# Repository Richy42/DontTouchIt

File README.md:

# DontTouchIt
Is an inductive distance sensor board based on the TI LDC1614 chip.

It is intended for 3d Printers to measure the distance to the printing bed.
It speeds up quad gantry levelling and bed mesh calibration as no z movement is needed to get the distance between the probe and the bed.

As it supports three sensors it could probably be used also for homing.

## The board

### Coils cut away and one mounted on an angle

### 3d Printed case in the size similar to an Omron (like) probe

### Mounted on an Voron 2.4

## Klipper 3D support
I added experimental support to klipper and the following video shows a Quad Gantry Level run
https://youtu.be/B2gruTA73uU

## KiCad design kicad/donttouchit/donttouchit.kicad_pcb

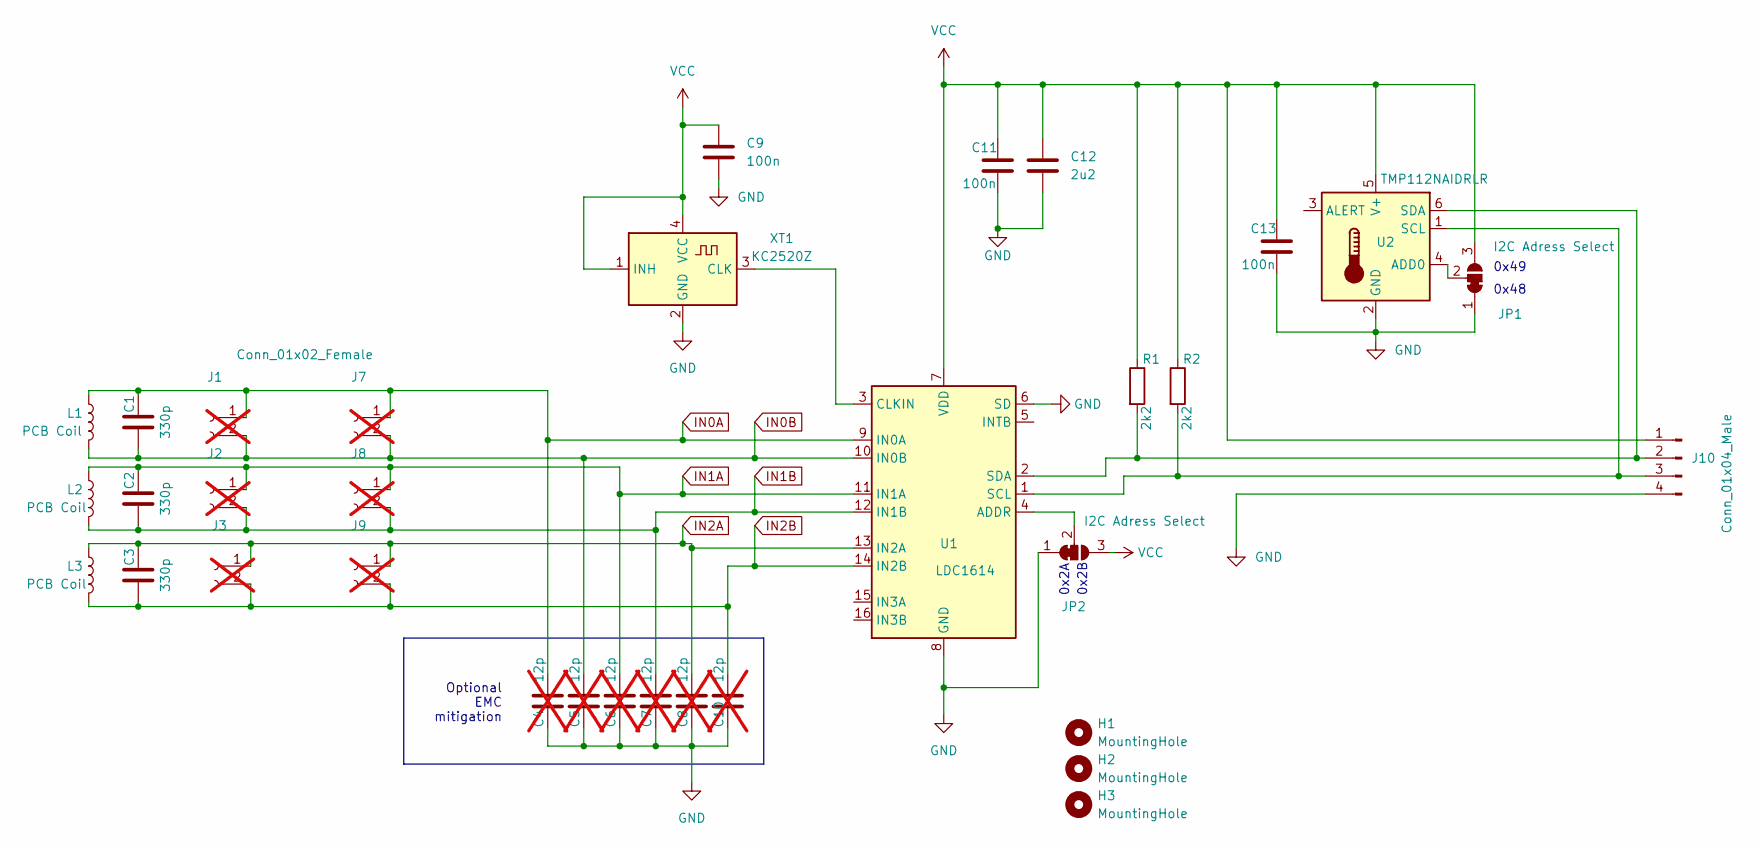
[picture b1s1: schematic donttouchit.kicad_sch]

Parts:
C1, C2, C3: 330p; C_0603_1608Metric_Pad1.08x0.95mm_HandSolder
C4, C5, C6, C7, C8, C10: 12p; C_0603_1608Metric_Pad1.08x0.95mm_HandSolder; not fitted
C9, C11, C13: 100n; C_0603_1608Metric_Pad1.08x0.95mm_HandSolder
C12: 2u2; C_0603_1608Metric_Pad1.08x0.95mm_HandSolder
H1, H2, H3: MountingHole; MountingHole_3.5mm
J1, J2, J3, J7, J8, J9: Conn_01x02_Female; PCBConnPadsTHT; not fitted
J10: Conn_01x04_Male; JST_PH_B4B-PH-SM4-TB_1x04-1MP_P2.00mm_Vertical
JP1, JP2: I2C Adress Select; SolderJumper-3_P1.3mm_Bridged12_RoundedPad1.0x1.5mm
L1, L2, L3: PCB Coil; Coil_14x14
R1, R2: 2k2; R_0603_1608Metric_Pad0.98x0.95mm_HandSolder
U1: LDC1614; WQFN-16-1EP_4x4mm_P0.5mm_EP2.6x2.6mm_ThermalVias
U2: TMP112NAIDRLR; SOT-563
XT1: KC2520Z; Oscillator_SMD_Kyocera_KC2520Z-4Pin_2.5x2.0mm

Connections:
GND: C4.2, C5.2, C6.2, C7.2, C8.2, C9.2, C10.2, C11.2, C12.2, C13.2, J10.4, JP1.1 (A), JP2.1 (A), U1.6 (SD), U1.8 (GND), U1.17 (GND), U2.2 (GND), XT1.2 (GND)
IN0A: C1.2, C4.1, J1.1, J7.1, L1.1, U1.9 (IN0A)
IN0B: C1.1, C5.1, J1.2, J7.2, L1.2, U1.10 (IN0B)
IN1A: C2.2, C6.1, J2.1, J8.1, L2.1, U1.11 (IN1A)
IN1B: C2.1, C7.1, J2.2, J8.2, L2.2, U1.12 (IN1B)
IN2A: C3.2, C8.1, J3.1, J9.1, L3.1, U1.13 (IN2A)
IN2B: C3.1, C10.1, J3.2, J9.2, L3.2, U1.14 (IN2B)
unnamed: J10.2, R1.2, U1.2 (SDA), U2.6 (SDA)
unnamed: J10.3, R2.2, U1.1 (SCL), U2.1 (SCL)
unnamed: JP1.2 (C), U2.4 (ADD0)
unnamed: JP2.2 (C), U1.4 (ADDR)
unnamed: U1.3 (CLKIN), XT1.3 (CLK)
VCC: C9.1, C11.1, C12.1, C13.1, J10.1, JP1.3 (B), JP2.3 (B), R1.1, R2.1, U1.7 (VDD), U2.5 (V+), XT1.1 (INH), XT1.4 (VCC)

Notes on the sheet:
0x48
0x2B
Optional EMC mitigation
0x2A
0x49

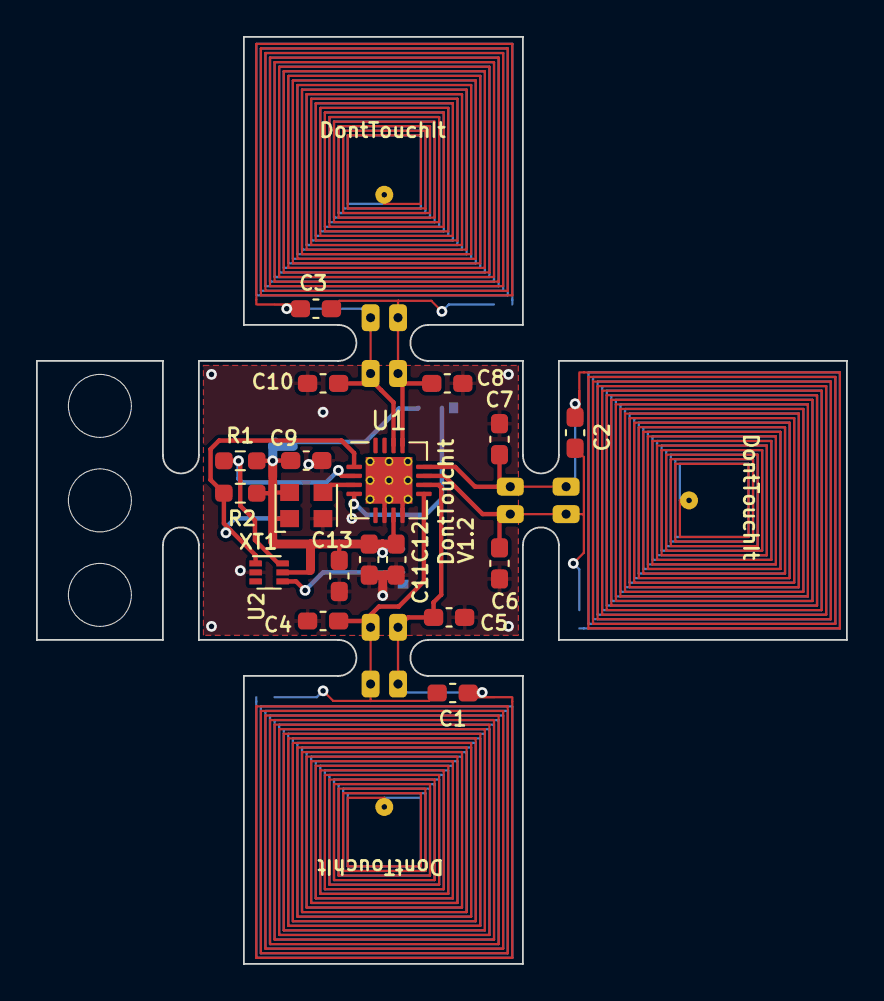
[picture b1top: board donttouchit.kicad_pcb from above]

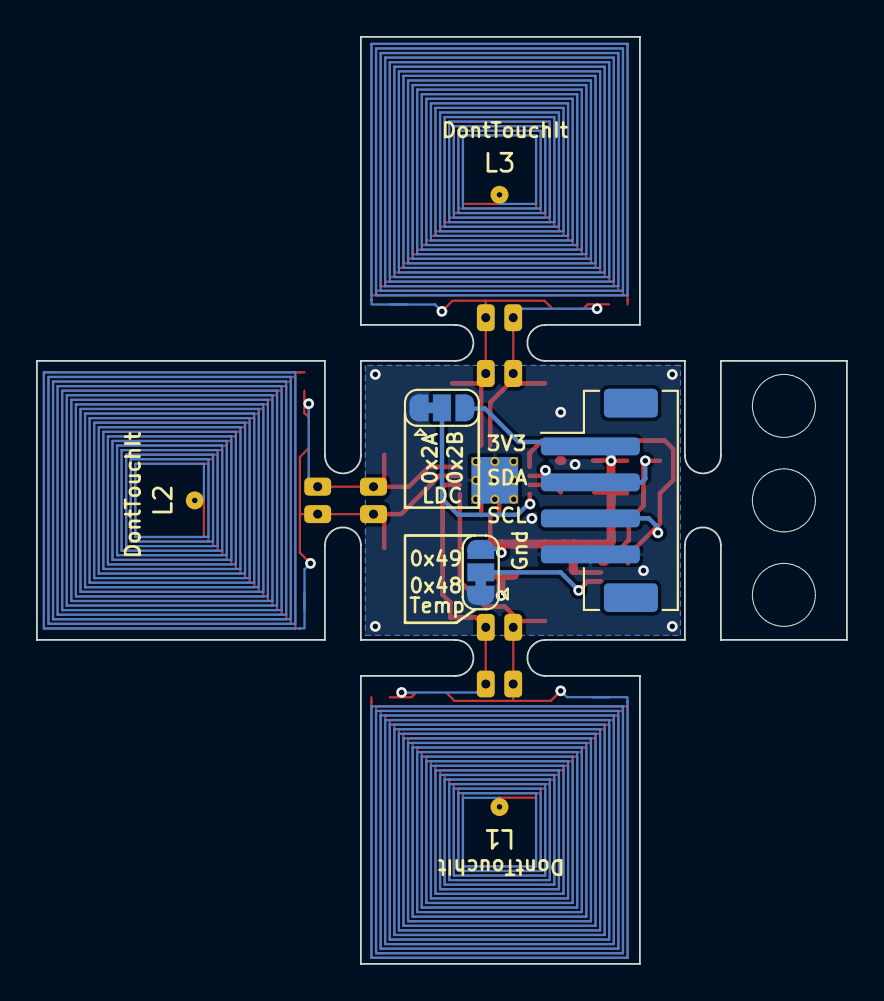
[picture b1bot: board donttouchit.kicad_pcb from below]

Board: 2 copper layers, 45.0 x 51.5 mm, 33 parts (6 on the bottom side), 13 nets.

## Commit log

2023-05-26 i2c pull up resistors added
2023-05-26 temperature sensor added
2023-06-08 I2C address solderbridges added / mounting hole added / size reduced for control section
2023-06-12 smaller formfactor that fits in the space of an Omron probe, 4th sensor pads removed
2023-06-17 ESD capacitor values corrected / Tempsensor name updated
2023-06-17 V1.2 fabrication files generated
2023-06-17 V1.1 fabrication files generated
